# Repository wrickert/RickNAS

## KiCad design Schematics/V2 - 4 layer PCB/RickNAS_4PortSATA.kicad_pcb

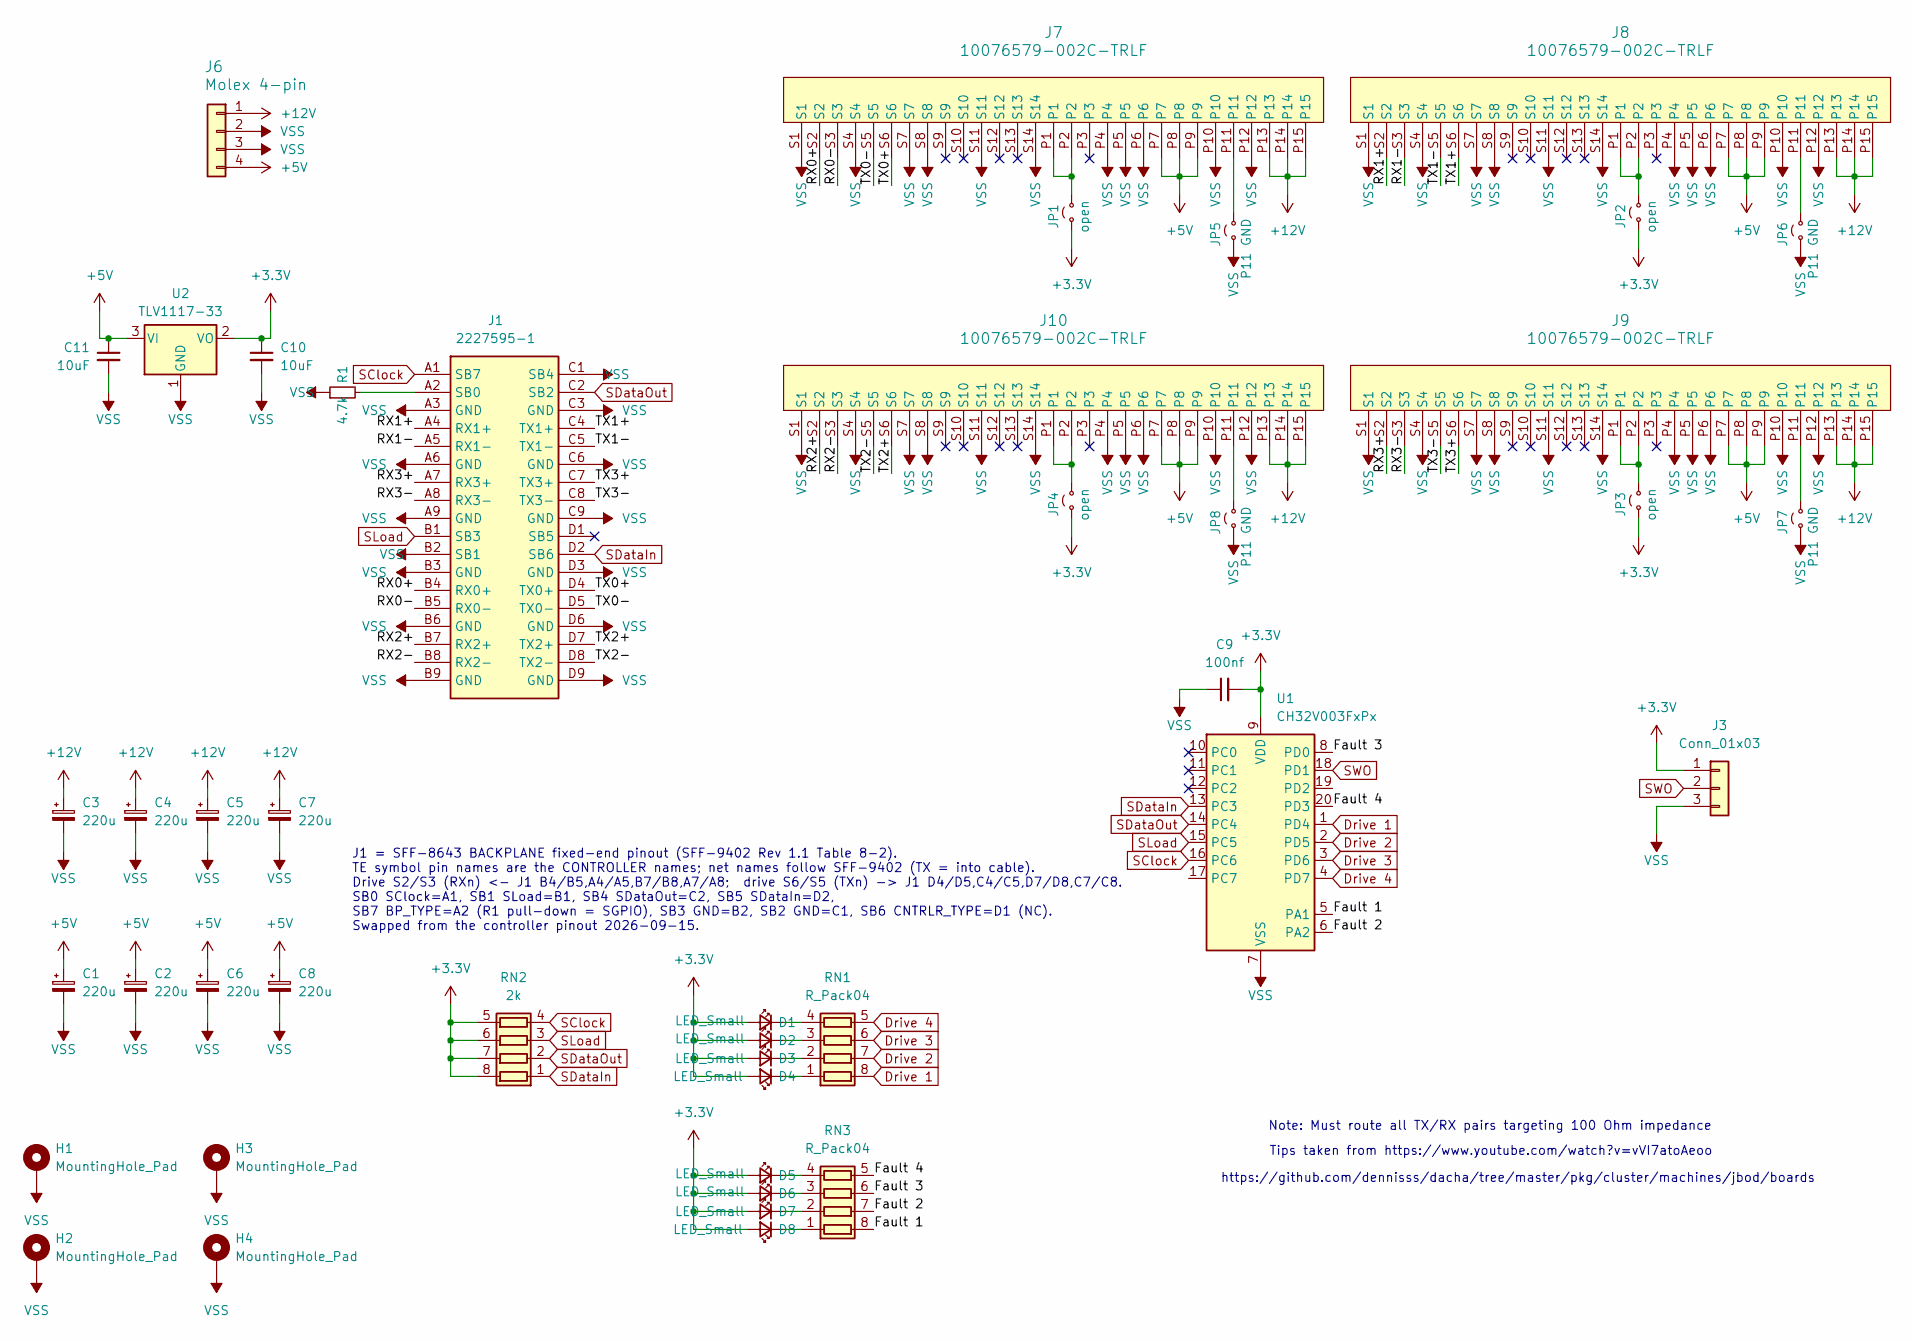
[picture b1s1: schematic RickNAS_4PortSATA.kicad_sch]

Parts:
C1, C2, C3, C4, C5, C6, C7, C8: 220u; CP_Radial_D10.0mm_P5.00mm
C9: 100nf; C_0805_2012Metric
C10, C11: 10uF; C_0805_2012Metric
D1, D2, D3, D4, D5, D6, D7, D8: LED_Small; LED_0805_2012Metric
H1, H2, H3, H4: MountingHole_Pad; MountingHole_3.2mm_M3_DIN965_Pad
J1: 2227595-1; 22275951; Manufacturer_Part_Number 2227595-1; Mouser Part Number 571-2227595-1
J3: Conn_01x03; PinHeader_1x03_P2.54mm_Vertical
J6: Molex 4-pin; TE_MATE-N-LOK_350211-1_1x04_P5.08mm_Vertical; MPN HC-C5080-4AS; LCSC C5221226
J7, J8, J9, J10: 10076579-002C-TRLF; 91908-291512_SAS_Conn
JP1, JP2, JP3, JP4: open; SolderJumper-2_P1.3mm_Open_TrianglePad1.0x1.5mm
JP5, JP6, JP7, JP8: P11 GND; SolderJumper-2_P1.3mm_Open_TrianglePad1.0x1.5mm
R1: 4.7k; R_0603_1608Metric
RN1, RN3: R_Pack04; R_Array_Concave_4x0603
RN2: 2k; R_Array_Concave_4x0603
U1: CH32V003FxPx; TSSOP-20_4.4x6.5mm_P0.65mm
U2: TLV1117-33; SOT-223-3_TabPin2

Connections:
+3.3V: C9.2, C10.1, D1.2 (A), D2.2 (A), D3.2 (A), D4.2 (A), D5.2 (A), D6.2 (A), D7.2 (A), D8.2 (A), J3.1, JP1.1 (A), JP2.1 (A), JP3.1 (A), JP4.1 (A), RN2.5 (R4.2), RN2.6 (R3.2), RN2.7 (R2.2), RN2.8 (R1.2), U1.9 (VDD), U2.2 (VO)
+5V: C1.1, C2.1, C6.1, C8.1, C11.1, J6.4, J7.P7, J7.P8, J7.P9, J8.P7, J8.P8, J8.P9, J9.P7, J9.P8, J9.P9, J10.P7, J10.P8, J10.P9, U2.3 (VI)
+12V: C3.1, C4.1, C5.1, C7.1, J6.1, J7.P13, J7.P14, J7.P15, J8.P13, J8.P14, J8.P15, J9.P13, J9.P14, J9.P15, J10.P13, J10.P14, J10.P15
/Fault 1: RN3.8 (R1.2), U1.5 (PA1)
/Fault 2: RN3.7 (R2.2), U1.6 (PA2)
/Fault 3: RN3.6 (R3.2), U1.8 (PD0)
/Fault 4: RN3.5 (R4.2), U1.20 (PD3)
/RX0+: J1.B4 (RX0+), J7.S2
/RX0-: J1.B5 (RX0-), J7.S3
/RX1+: J1.A4 (RX1+), J8.S2
/RX1-: J1.A5 (RX1-), J8.S3
/RX2+: J1.B7 (RX2+), J10.S2
/RX2-: J1.B8 (RX2-), J10.S3
/RX3+: J1.A7 (RX3+), J9.S2
/RX3-: J1.A8 (RX3-), J9.S3
/TX0+: J1.D4 (TX0+), J7.S6
/TX0-: J1.D5 (TX0-), J7.S5
/TX1+: J1.C4 (TX1+), J8.S6
/TX1-: J1.C5 (TX1-), J8.S5
/TX2+: J1.D7 (TX2+), J10.S6
/TX2-: J1.D8 (TX2-), J10.S5
/TX3+: J1.C7 (TX3+), J9.S6
/TX3-: J1.C8 (TX3-), J9.S5
Drive 1: RN1.8 (R1.2), U1.1 (PD4)
Drive 2: RN1.7 (R2.2), U1.2 (PD5)
Drive 3: RN1.6 (R3.2), U1.3 (PD6)
Drive 4: RN1.5 (R4.2), U1.4 (PD7)
unnamed: D1.1 (K), RN1.4 (R4.1)
unnamed: D2.1 (K), RN1.3 (R3.1)
unnamed: D3.1 (K), RN1.2 (R2.1)
unnamed: D4.1 (K), RN1.1 (R1.1)
unnamed: D5.1 (K), RN3.4 (R4.1)
unnamed: D6.1 (K), RN3.3 (R3.1)
unnamed: D7.1 (K), RN3.2 (R2.1)
unnamed: D8.1 (K), RN3.1 (R1.1)
unnamed: J1.A2 (SB0), R1.2
unnamed: J7.P1, J7.P2, JP1.2 (B)
unnamed: J8.P1, J8.P2, JP2.2 (B)
unnamed: J9.P1, J9.P2, JP3.2 (B)
unnamed: J10.P1, J10.P2, JP4.2 (B)
unnamed: J7.P11, JP5.2 (B)
unnamed: J8.P11, JP6.2 (B)
unnamed: J9.P11, JP7.2 (B)
unnamed: J10.P11, JP8.2 (B)
SClock: J1.A1 (SB7), RN2.4 (R4.1), U1.16 (PC6)
SDataIn: J1.D2 (SB6), RN2.1 (R1.1), U1.13 (PC3)
SDataOut: J1.C2 (SB2), RN2.2 (R2.1), U1.14 (PC4)
SLoad: J1.B1 (SB3), RN2.3 (R3.1), U1.15 (PC5)
SWO: J3.2, U1.18 (PD1)
VSS: C1.2, C2.2, C3.2, C4.2, C5.2, C6.2, C7.2, C8.2, C9.1, C10.2, C11.2, H1.1 (1_1), H2.1 (1_1), H3.1 (1_1), H4.1 (1_1), J1.A3 (GND), J1.A6 (GND), J1.A9 (GND), J1.B2 (SB1), J1.B3 (GND), J1.B6 (GND), J1.B9 (GND), J1.C1 (SB4), J1.C3 (GND), J1.C6 (GND), J1.C9 (GND), J1.D3 (GND), J1.D6 (GND), J1.D9 (GND), J3.3, J6.2, J6.3, J7.P4, J7.P5, J7.P6, J7.P10, J7.P12, J7.S1, J7.S4, J7.S7, J7.S8, J7.S11, J7.S14, J8.P4, J8.P5, J8.P6, J8.P10, J8.P12, J8.S1, J8.S4, J8.S7, J8.S8, J8.S11, J8.S14, J9.P4, J9.P5, J9.P6, J9.P10, J9.P12, J9.S1, J9.S4, J9.S7, J9.S8, J9.S11, J9.S14, J10.P4, J10.P5, J10.P6, J10.P10, J10.P12, J10.S1, J10.S4, J10.S7, J10.S8, J10.S11, J10.S14, JP5.1 (A), JP6.1 (A), JP7.1 (A), JP8.1 (A), R1.1, U1.7 (VSS), U2.1 (GND)

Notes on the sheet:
https://github.com/dennisss/dacha/tree/master/pkg/cluster/machines/jbod/boards
Tips taken from https://www.youtube.com/watch?v=vVI7atoAeoo
Note: Must route all TX/RX pairs targeting 100 Ohm impedance
J1 = SFF-8643 BACKPLANE fixed-end pinout (SFF-9402 Rev 1.1 Table 8-2). TE symbol pin names are the CONTROLLER names; net names follow SFF-9402 (TX = into cable). Drive S2/S3 (RXn) <- J1 B4/B5,A4/A5,B7/B8,A7/A8; drive S6/S5 (TXn) -> J1 D4/D5,C4/C5,D7/D8,C7/C8. SB0 SClock=A1, SB1 SLoad=B1, SB4 SDataO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

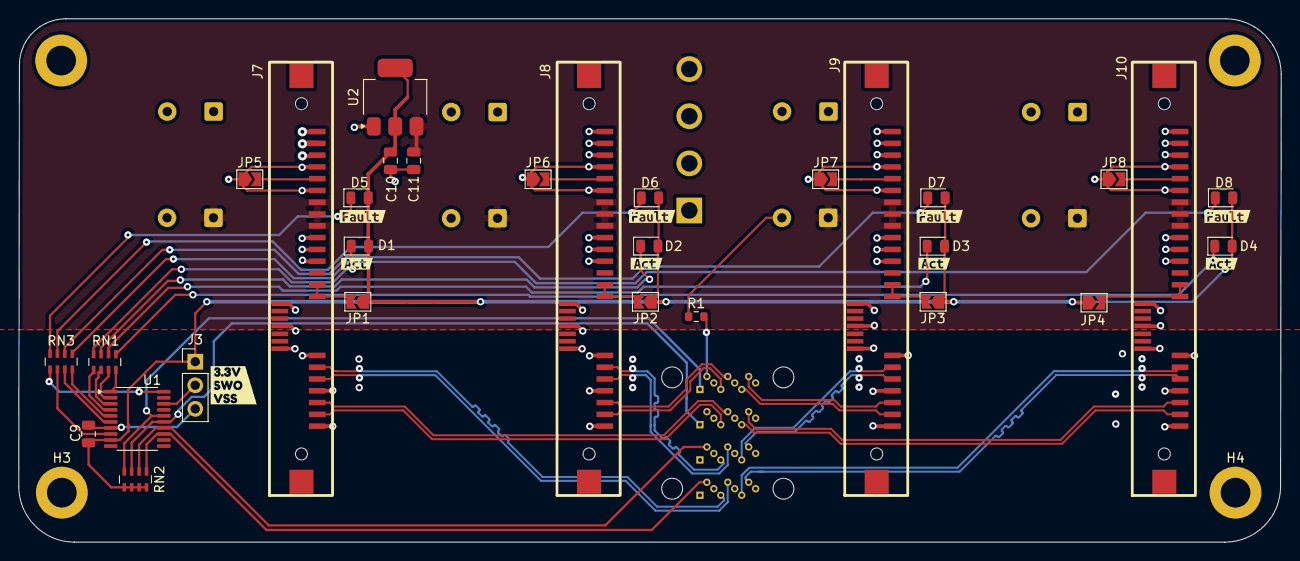
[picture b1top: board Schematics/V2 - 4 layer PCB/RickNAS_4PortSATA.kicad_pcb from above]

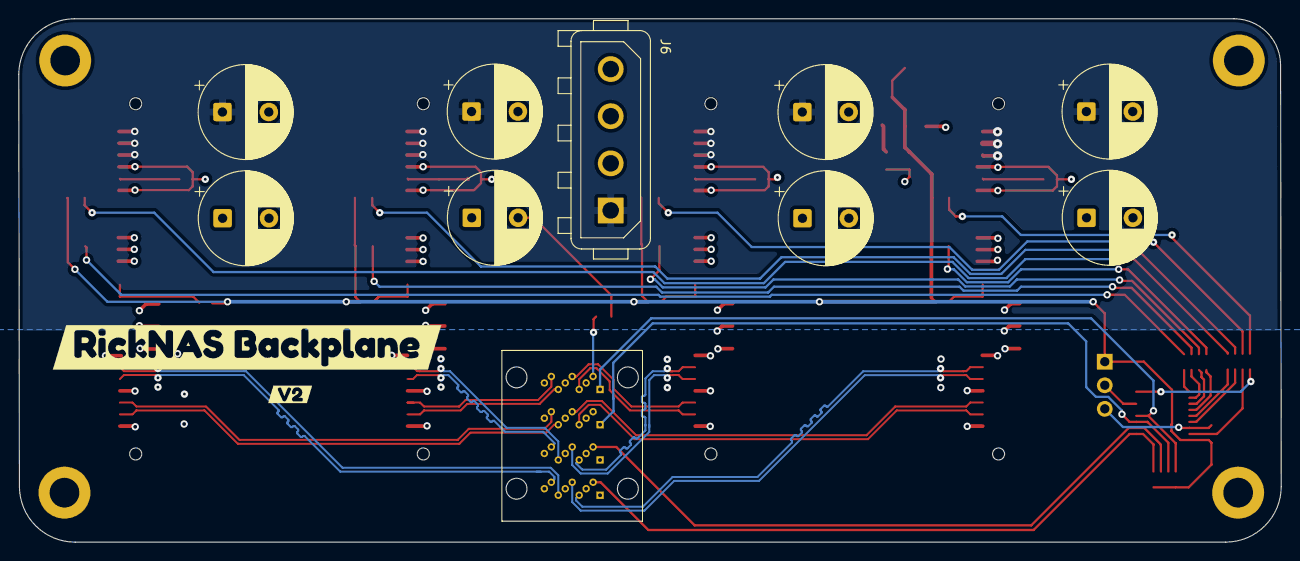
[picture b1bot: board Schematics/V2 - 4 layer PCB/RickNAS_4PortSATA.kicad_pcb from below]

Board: 4 copper layers, 136.1 x 56.4 mm, 55 parts (12 on the bottom side), 50 nets.

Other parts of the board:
kibuzzard-6AAAB40B: G***; kibuzzard-6AAAB40B
kibuzzard-6AAAB169, kibuzzard-6AAAB169#2, kibuzzard-6AAAB169#3, kibuzzard-6AAAB169#4: G***; kibuzzard-6AAAB169
kibuzzard-6AAAB175, kibuzzard-6AAAB175#2, kibuzzard-6AAAB175#3, kibuzzard-6AAAB175#4: G***; kibuzzard-6AAAB175
kibuzzard-6AAAC547: G***; kibuzzard-6AAAC547
kibuzzard-69861090: G***; kibuzzard-69861090

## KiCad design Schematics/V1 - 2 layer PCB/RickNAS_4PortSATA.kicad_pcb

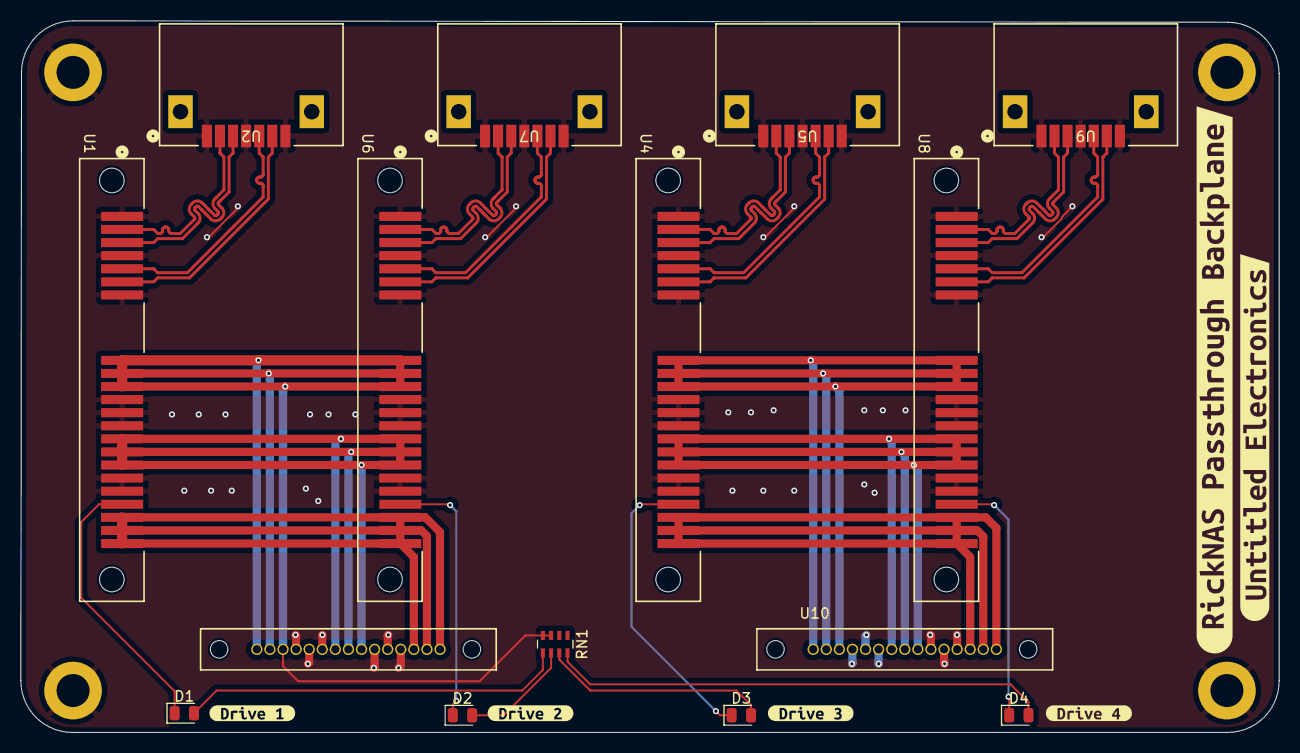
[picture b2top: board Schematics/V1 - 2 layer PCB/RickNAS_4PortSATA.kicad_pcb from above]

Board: 2 copper layers, 122.1 x 69.1 mm, 25 parts (0 on the bottom side), 31 nets.

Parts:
D1, D2, D3, D4: LED_Small; LED_0805_2012Metric
H1, H2, H3, H4: MountingHole_Pad; MountingHole_3.2mm_M3_DIN965_Pad
RN1: R_Pack04; R_Array_Concave_4x0603
U1, U4, U6, U8: SATA_Combined; CONN22_877811_MOL
U2, U5, U7, U9: SATA_Data; CONN_67490-1220_MOL
U3, U10: SATA_Power; alim_SATA
kibuzzard-67B4AC4E: G***; kibuzzard-67B4AC4E
kibuzzard-67B605A5: G***; kibuzzard-67B605A5
kibuzzard-67B605B2: G***; kibuzzard-67B605B2
kibuzzard-67B6042A: G***; kibuzzard-67B6042A
kibuzzard-67B60589: G***; kibuzzard-67B60589
kibuzzard-67B60597: G***; kibuzzard-67B60597

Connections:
+3.3V: RN1.1 (R1.1), RN1.2 (R2.1), RN1.3 (R3.1), RN1.4 (R4.1), U1.8 (3.3V), U1.9 (3.3V), U1.10 (3.3V), U3.1 (3.3V), U3.2 (3.3V), U3.3 (3.3V), U6.8 (3.3V), U6.9 (3.3V), U6.10 (3.3V)
+3.3VP: U4.8 (3.3V), U4.9 (3.3V), U4.10 (3.3V), U8.8 (3.3V), U8.9 (3.3V), U8.10 (3.3V), U10.1 (3.3V), U10.2 (3.3V), U10.3 (3.3V)
+5P: U4.14 (5V), U4.15 (5V), U4.16 (5V), U8.14 (5V), U8.15 (5V), U8.16 (5V), U10.7 (5V), U10.8 (5V), U10.9 (5V)
+5V: U1.14 (5V), U1.15 (5V), U1.16 (5V), U3.7 (5V), U3.8 (5V), U3.9 (5V), U6.14 (5V), U6.15 (5V), U6.16 (5V)
+12P: U4.20 (12V), U4.21 (12V), U4.22 (12V), U8.20 (12V), U8.21 (12V), U8.22 (12V), U10.13 (12V), U10.14 (12V), U10.15 (12V)
+12V: U1.20 (12V), U1.21 (12V), U1.22 (12V), U3.13 (12V), U3.14 (12V), U3.15 (12V), U6.20 (12V), U6.21 (12V), U6.22 (12V)
/A1+: U4.2 (A+), U5.2 (A+)
/A1-: U4.3 (A-), U5.3 (A-)
/A2+: U6.2 (A+), U7.2 (A+)
/A2-: U6.3 (A-), U7.3 (A-)
/A3+: U8.2 (A+), U9.2 (A+)
/A3-: U8.3 (A-), U9.3 (A-)
/A+: U1.2 (A+), U2.2 (A+)
/A-: U1.3 (A-), U2.3 (A-)
/B1+: U4.6 (B+), U5.6 (B+)
/B1-: U4.5 (B-), U5.5 (B-)
/B2+: U6.6 (B+), U7.6 (B+)
/B2-: U6.5 (B-), U7.5 (B-)
/B3+: U8.6 (B+), U9.6 (B+)
/B3-: U8.5 (B-), U9.5 (B-)
/B+: U1.6 (B+), U2.6 (B+)
/B-: U1.5 (B-), U2.5 (B-)
Drive 1: D1.1 (K), U1.19 (VSS)
Drive 2: D2.1 (K), U6.19 (VSS)
Drive 3: D3.1 (K), U4.19 (VSS)
Drive 4: D4.1 (K), U8.19 (VSS)
unnamed: D1.2 (A), RN1.5 (R4.2)
unnamed: D2.2 (A), RN1.6 (R3.2)
unnamed: D3.2 (A), RN1.7 (R2.2)
unnamed: D4.2 (A), RN1.8 (R1.2)
VSS: H1.1, H2.1, H3.1, H4.1, U1.1 (VSS), U1.4 (VSS), U1.7 (VSS), U1.11 (VSS), U1.12 (VSS), U1.13 (VSS), U1.17 (VSS), U1.18 (VSS), U2.1 (VSS), U2.4 (VSS), U2.7 (VSS), U3.4 (VSS), U3.5 (VSS), U3.6 (VSS), U3.10 (VSS), U3.11 (VSS), U3.12 (VSS), U4.1 (VSS), U4.4 (VSS), U4.7 (VSS), U4.11 (VSS), U4.12 (VSS), U4.13 (VSS), U4.17 (VSS), U4.18 (VSS), U5.1 (VSS), U5.4 (VSS), U5.7 (VSS), U6.1 (VSS), U6.4 (VSS), U6.7 (VSS), U6.11 (VSS), U6.12 (VSS), U6.13 (VSS), U6.17 (VSS), U6.18 (VSS), U7.1 (VSS), U7.4 (VSS), U7.7 (VSS), U8.1 (VSS), U8.4 (VSS), U8.7 (VSS), U8.11 (VSS), U8.12 (VSS), U8.13 (VSS), U8.17 (VSS), U8.18 (VSS), U9.1 (VSS), U9.4 (VSS), U9.7 (VSS), U10.4 (VSS), U10.5 (VSS), U10.6 (VSS), U10.10 (VSS), U10.11 (VSS), U10.12 (VSS)

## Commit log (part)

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2025-02-07 Schematic done
2025-02-10 Assigned some footprints. Where is that sata power part?
2025-02-14 Almost there'
2025-02-18 Ordering PCBs
2025-03-04 Started CAD
2025-03-09 Motherboard secured
2026-01-15 Progress on V2
2026-01-16 Progress on routing
2026-02-06 V2 finished, ordering PCB
2026-04-10 Lets build some boards
